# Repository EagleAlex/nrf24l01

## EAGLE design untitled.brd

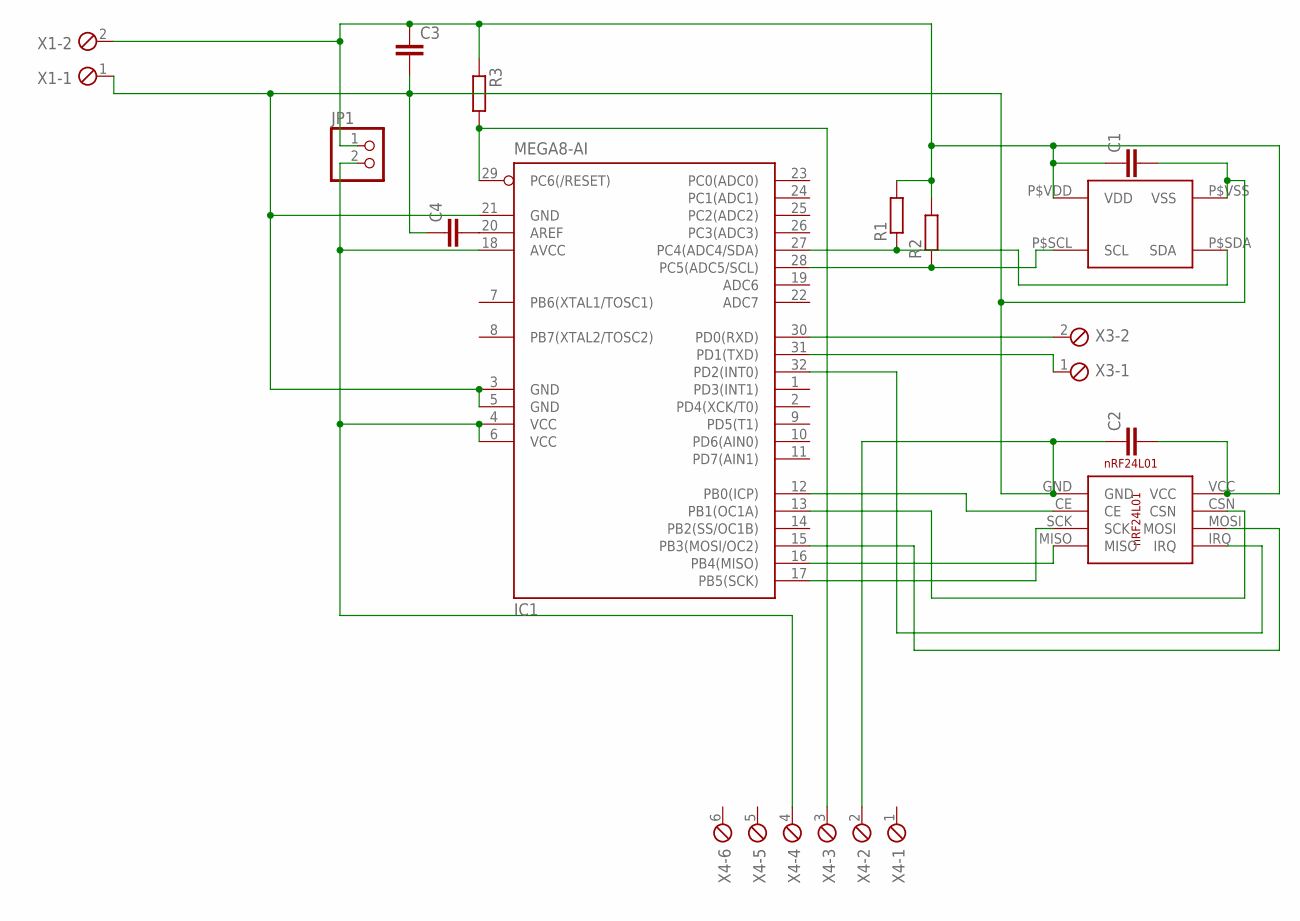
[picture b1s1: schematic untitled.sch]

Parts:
C1: C-EUC1206; C1206
C2: C-EUC0805; C0805
C3: C-EU025-060X050; C025-060X050
C4: C-EUC0805K; C0805K
IC1: MEGA8-AI; TQFP32-08
JP1: PINHD-1X2; 1X02
R1, R2, R3: R-EU_R0805; R0805
U$1: SHT21; DFN6
U$2: NRF24L01B; B1
X1, X3: MPT2; 2POL254
X4: MPT6; 6POL254

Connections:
unnamed: IC1.32 (PD2(INT0)), U$2.IRQ
unnamed: IC1.15 (PB3(MOSI/OC2)), U$2.MOSI
unnamed: IC1.17 (PB5(SCK)), U$2.SCK
unnamed: IC1.16 (PB4(MISO)), U$2.MISO
unnamed: IC1.12 (PB0(ICP)), U$2.CE
unnamed: IC1.13 (PB1(OC1A)), U$2.CSN
unnamed: IC1.28 (PC5(ADC5/SCL)), R2.1, U$1.P$SCL (SCL)
unnamed: IC1.27 (PC4(ADC4/SDA)), R1.1, U$1.P$SDA (SDA)
unnamed: IC1.4 (VCC), IC1.6 (VCC), IC1.18 (AVCC), JP1.2, X4.4
unnamed: C4.2, IC1.20 (AREF)
unnamed: C1.2, C2.1, C3.2, C4.1, IC1.3 (GND), IC1.5 (GND), IC1.21 (GND), U$1.P$VSS (VSS), U$2.GND, X1.1, X4.2
unnamed: C1.1, C2.2, C3.1, JP1.1, R1.2, R2.2, R3.1, U$1.P$VDD (VDD), U$2.VCC, X1.2
unnamed: IC1.29 (PC6(/RESET)), R3.2, X4.3
unnamed: IC1.30 (PD0(RXD)), X3.2
unnamed: IC1.31 (PD1(TXD)), X3.1

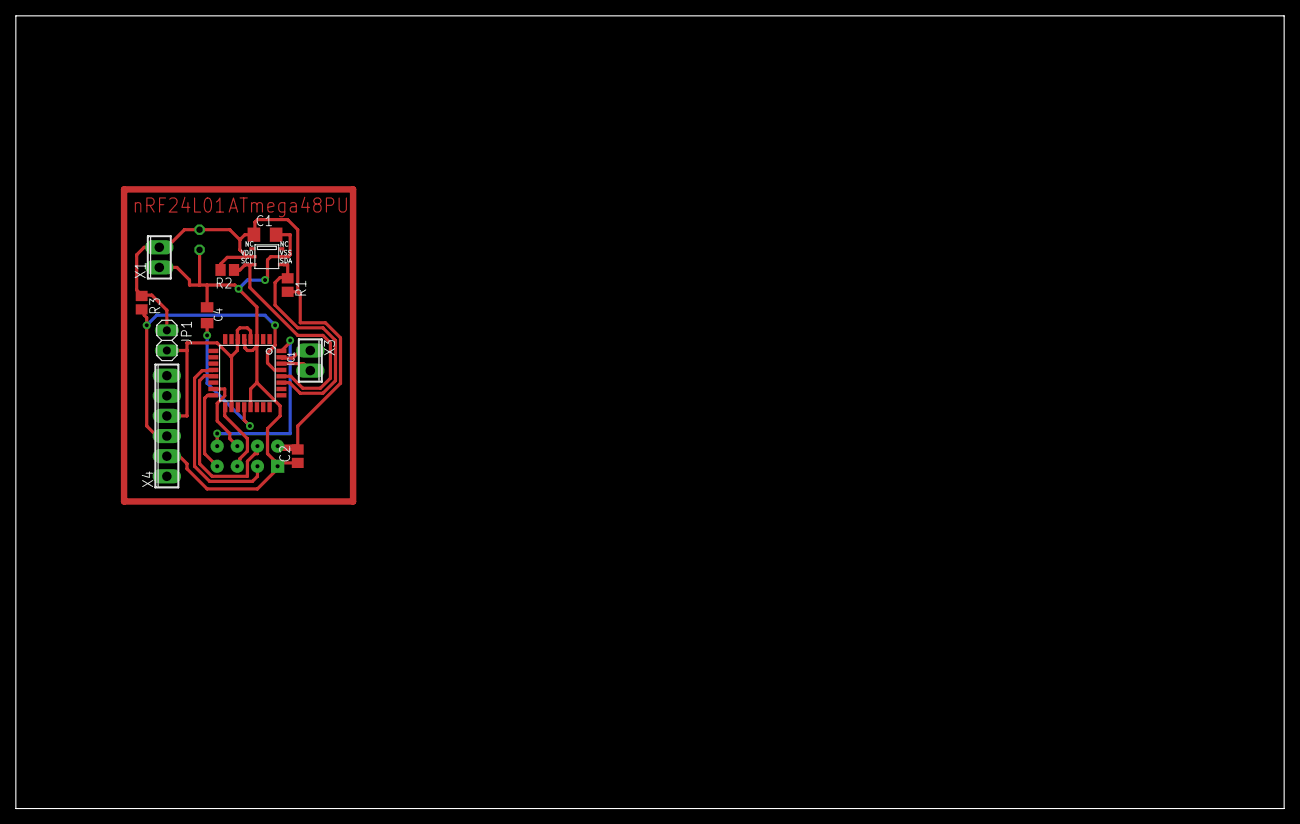
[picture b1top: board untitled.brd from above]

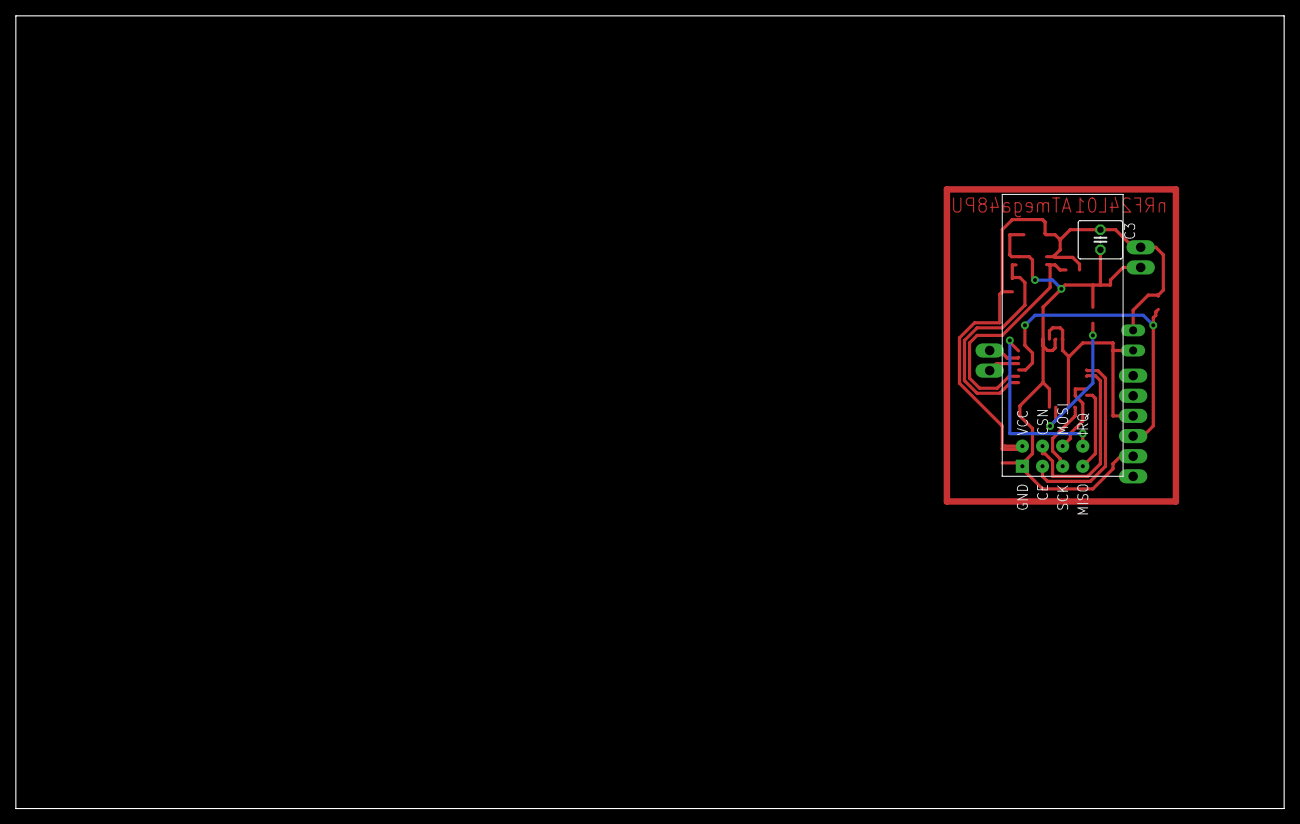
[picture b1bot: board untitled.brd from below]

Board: 2 copper layers, 160.0 x 100.0 mm, 14 parts (2 on the bottom side), 15 nets.

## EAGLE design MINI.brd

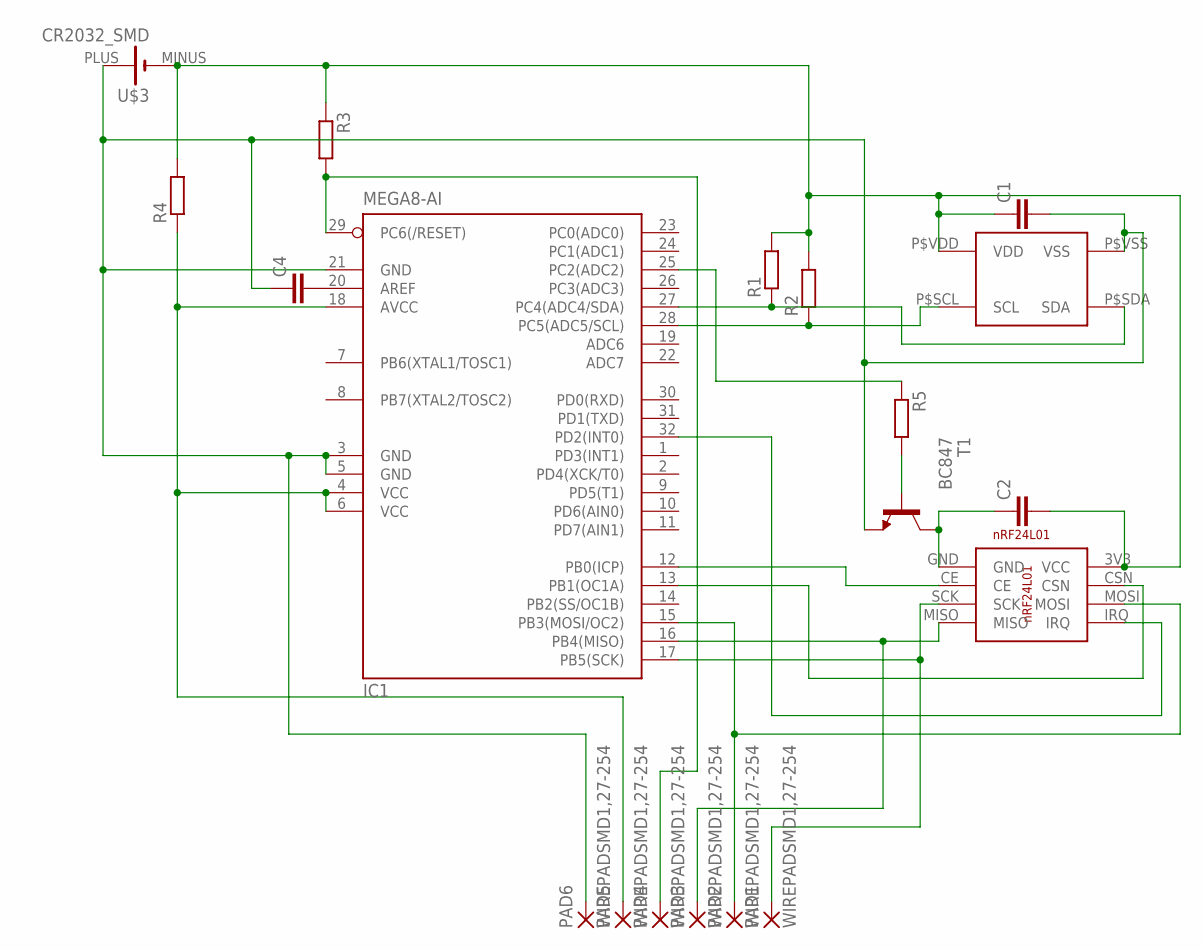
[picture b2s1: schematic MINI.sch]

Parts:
C1: C-EUC0805K; C0805K
C2, C4: C-EUC0805; C0805
IC1: MEGA8-AI; TQFP32-08
MINI1: NRF24L01BMINI; MINI
PAD1, PAD2, PAD3, PAD4, PAD5, PAD6: WIREPADSMD1,27-254; SMD1,27-2,54
R1, R2: R-EU_R1206W; R1206W
R3: R-EU_R0805; R0805
R4: R-EU_R1206; R1206
R5: R-EU_R0805W; R0805W
T1: BC847; SOT23
U$1: SHT21; DFN6
U$3: CR2032_SMD

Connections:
unnamed: IC1.32 (PD2(INT0)), MINI1.IRQ
unnamed: IC1.15 (PB3(MOSI/OC2)), MINI1.MOSI, PAD2.1
unnamed: IC1.17 (PB5(SCK)), MINI1.SCK, PAD1.1
unnamed: IC1.16 (PB4(MISO)), MINI1.MISO, PAD3.1
unnamed: IC1.12 (PB0(ICP)), MINI1.CE
unnamed: IC1.13 (PB1(OC1A)), MINI1.CSN
unnamed: IC1.28 (PC5(ADC5/SCL)), R2.1, U$1.P$SCL (SCL)
unnamed: IC1.27 (PC4(ADC4/SDA)), R1.1, U$1.P$SDA (SDA)
unnamed: IC1.4 (VCC), IC1.6 (VCC), IC1.18 (AVCC), PAD5.1, R4.1
unnamed: C2.1, MINI1.GND, T1.3 (C)
unnamed: C4.2, IC1.20 (AREF)
unnamed: C1.2, C4.1, IC1.3 (GND), IC1.5 (GND), IC1.21 (GND), PAD6.1, T1.2 (E), U$1.P$VSS (VSS), U$3.PLUS (+)
unnamed: IC1.25 (PC2(ADC2)), R5.1
unnamed: C1.1, C2.2, MINI1.3V3 (VCC), R1.2, R2.2, R3.1, R4.2, U$1.P$VDD (VDD), U$3.MINUS (-)
unnamed: IC1.29 (PC6(/RESET)), PAD4.1, R3.2
unnamed: R5.2, T1.1 (B)

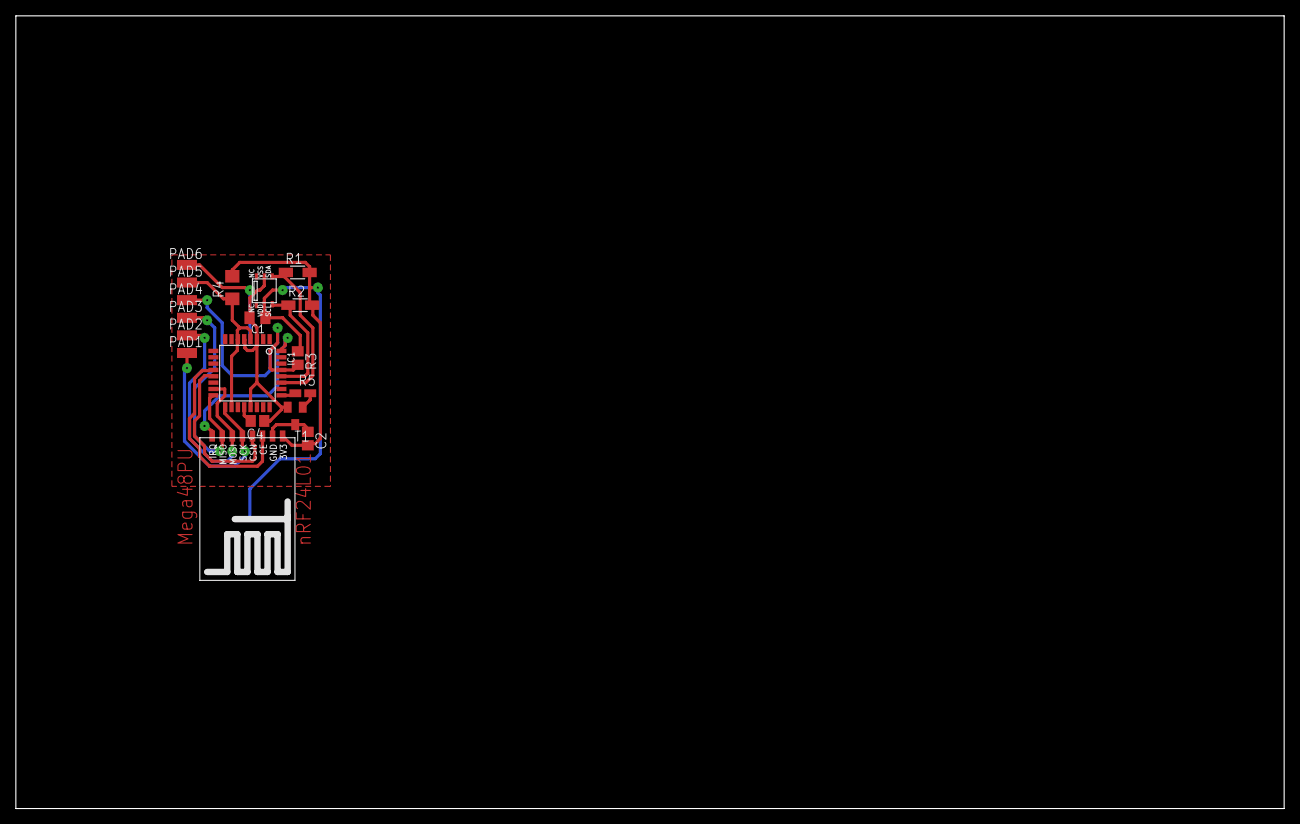
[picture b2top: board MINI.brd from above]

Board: 2 copper layers, 160.0 x 100.0 mm, 19 parts (1 on the bottom side), 16 nets.

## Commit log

2016-05-15 :neckbeard: Added .gitattributes & .gitignore files
